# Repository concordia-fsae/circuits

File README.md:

# Circuit Repo
Will contain all of the circuits for the car

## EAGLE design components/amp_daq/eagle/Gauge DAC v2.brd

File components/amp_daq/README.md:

# Strain Gauge Amp Daq Module

Module designed to take in data from strain gauges and ouput over CAN to the Motec.

The last iteration was designed in Eagle (and works), but we will be redesigning in Altium and adding some functionality

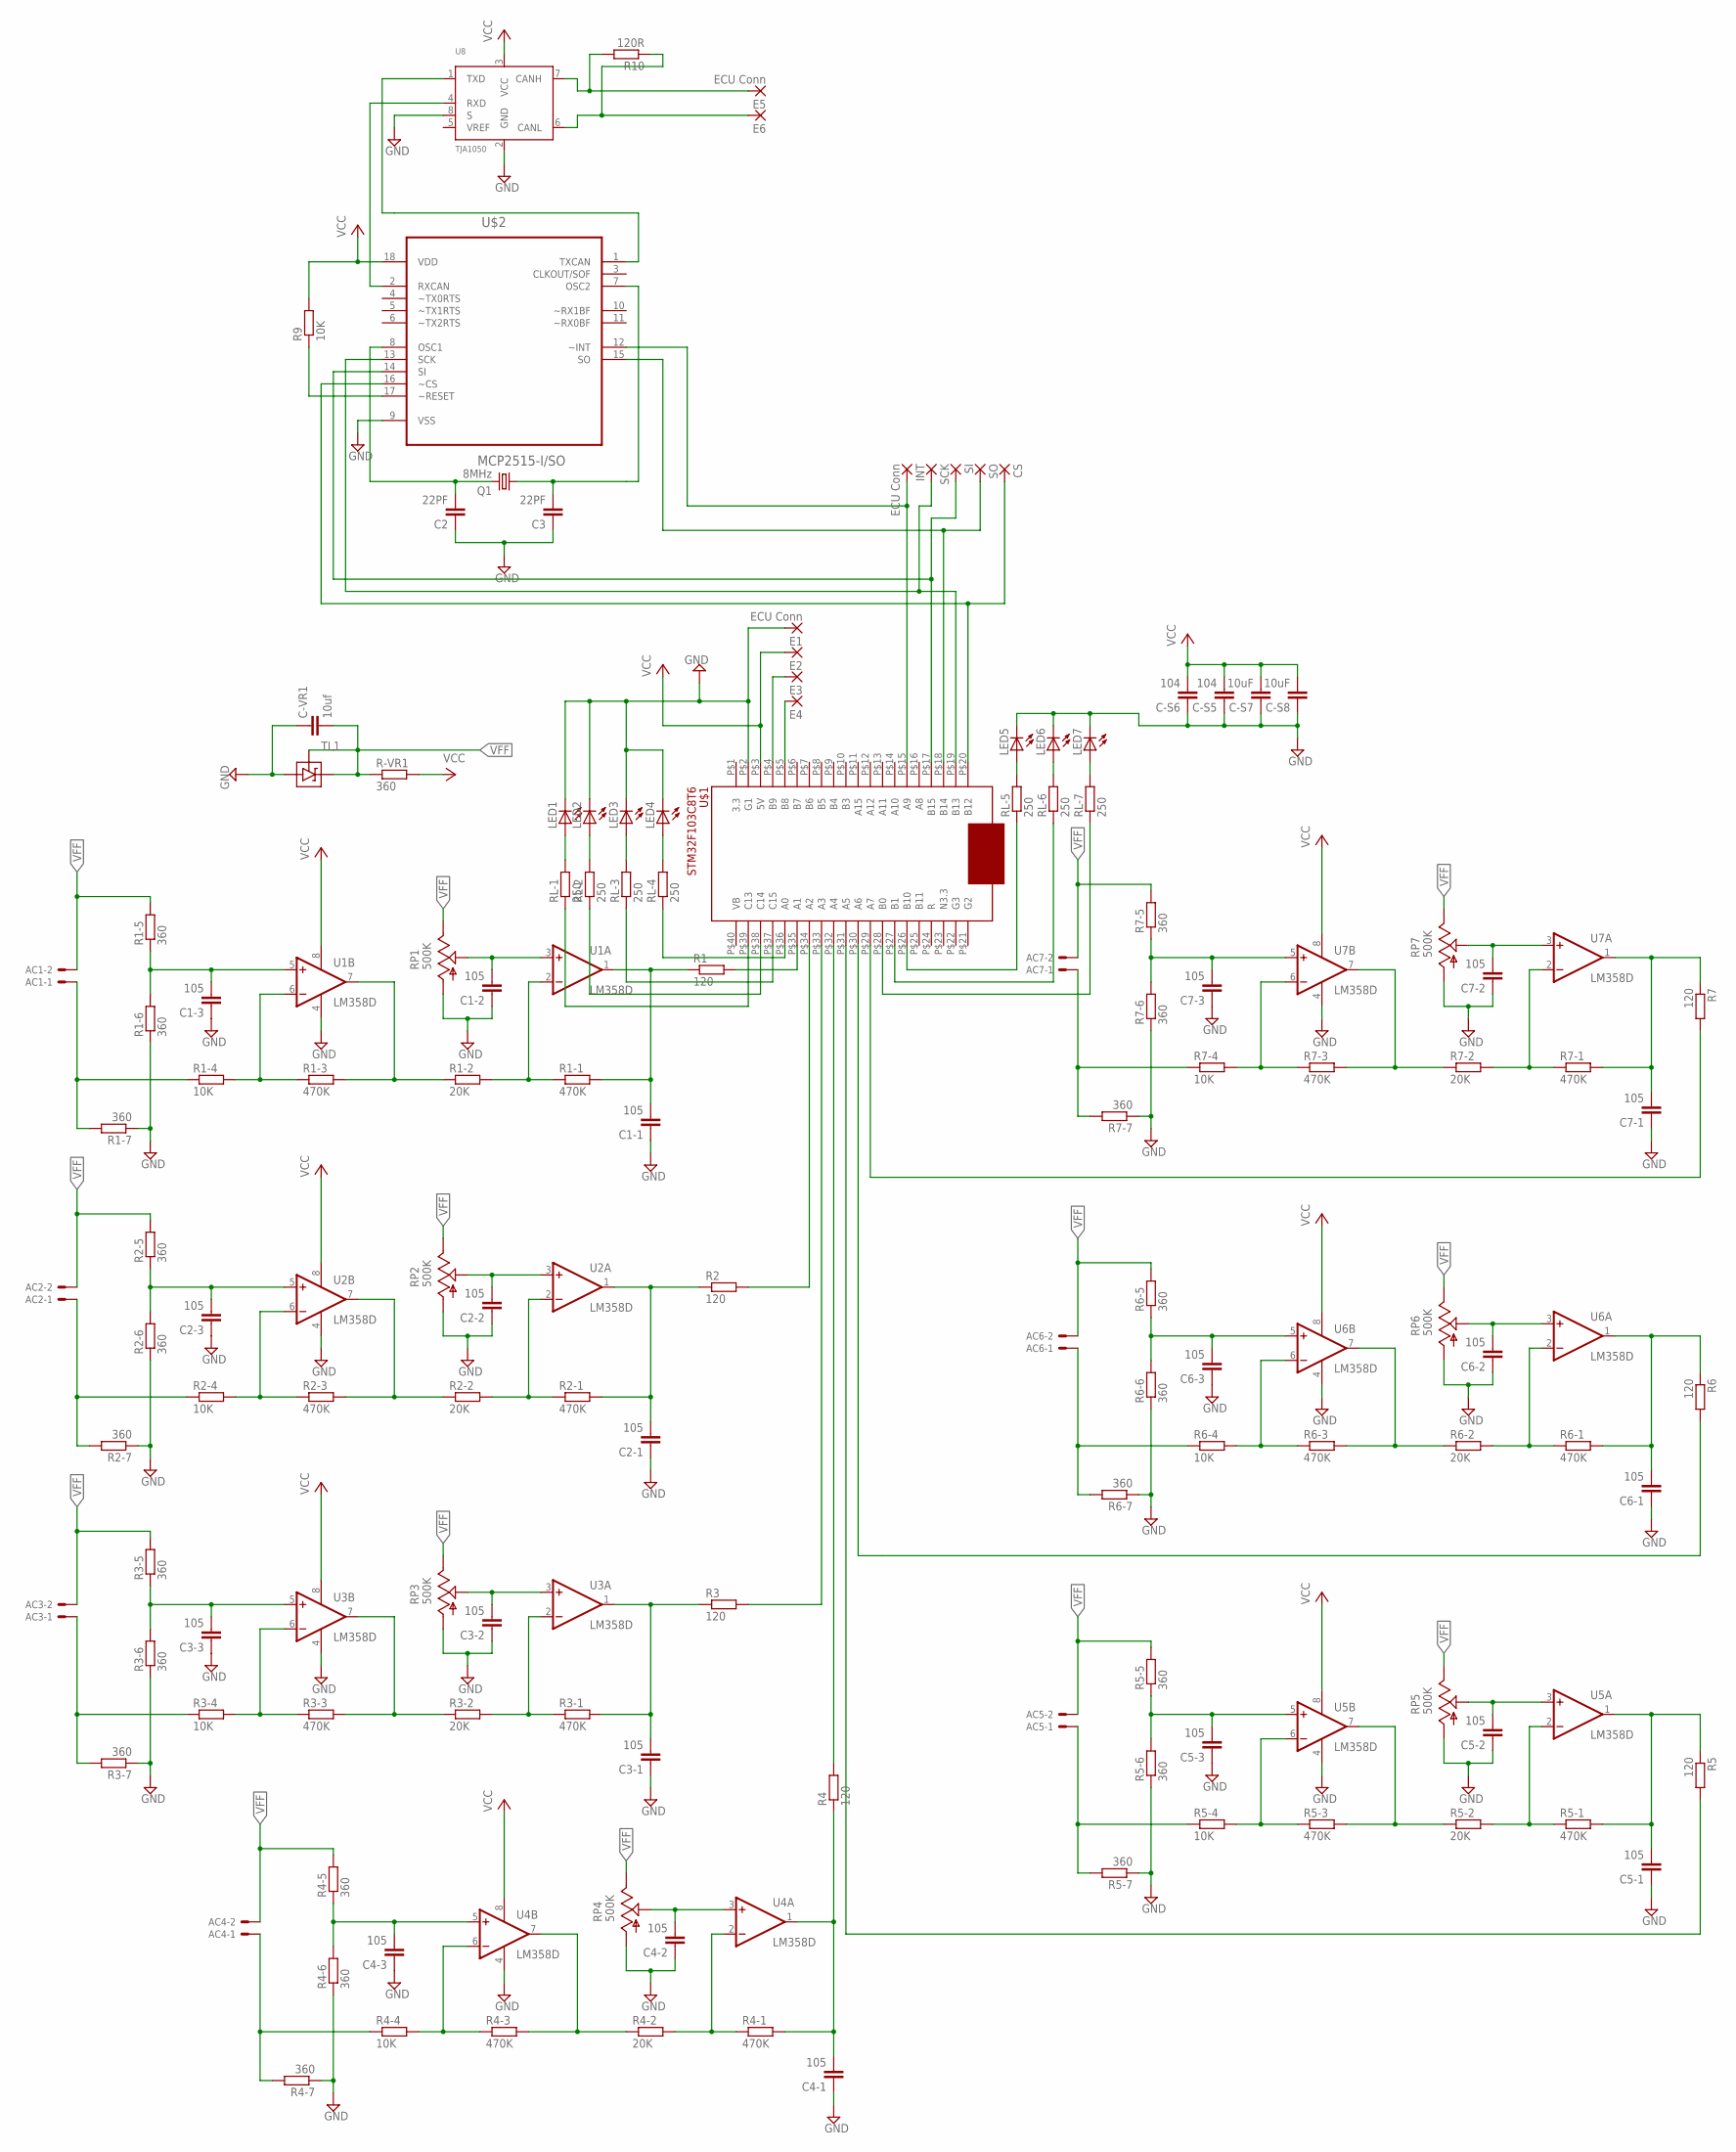
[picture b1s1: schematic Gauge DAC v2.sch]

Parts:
AC1, AC2, AC3, AC4, AC5, AC6, AC7: JST-XH-02-PIN-ROUND-PAD; JST-XH-02-PACKAGE-ROUND-PAD
C1-1, C1-2, C1-3, C2-1, C2-2, C2-3, C3-1, C3-2, C3-3, C4-1, C4-2, C4-3, C5-1, C5-2, C5-3, C6-1, C6-2, C6-3, C7-1, C7-2, C7-3: 105; C0805
C2, C3: 22PF; C0805
C-S5, C-S6: 104; C0805
C-S7, C-S8: 10uF; C0805
C-VR1: 10uf; C0805
CS: WIREPADSMD1,27-254; SMD1,27-2,54
E1, E5: ECU Conn; SMD1,27-2,54
E2, E3, E4: WIREPADSMD1,27-254; SMD1,27-2,54
E6: SMD1,27-2,54
INT: ECU Conn; SMD1,27-2,54
LED1, LED2, LED3, LED4, LED5, LED6, LED7: LEDCHIP-LED0805; CHIP-LED0805
Q1: 8MHz; HC49/S
R1, R2, R3, R4, R5, R6, R7: 120; M0805
R1-1, R1-3, R2-1, R2-3, R3-1, R3-3, R4-1, R4-3, R5-1, R5-3, R6-1, R6-3, R7-1, R7-3: 470K; M0805
R1-2, R2-2, R3-2, R4-2, R5-2, R6-2, R7-2: 20K; M0805
R1-4, R2-4, R3-4, R4-4, R5-4, R6-4, R7-4, R9: 10K; M0805
R1-5, R1-6, R1-7, R2-5, R2-6, R2-7, R3-5, R3-6, R3-7, R4-5, R4-6, R4-7, R5-5, R5-6, R5-7, R6-5, R6-6, R6-7, R7-5, R7-6, R7-7: 360; M0805
R10: 120R; M0805
R-VR1: 360; M0805
RL-1, RL-2, RL-3, RL-4, RL-5, RL-6, RL-7: 250; M0805
RP1, RP2, RP3, RP4, RP5, RP6, RP7: 500K; B64Y
SCK: WIREPADSMD1,27-254; SMD1,27-2,54
SI: WIREPADSMD1,27-254; SMD1,27-2,54
SO: WIREPADSMD1,27-254; SMD1,27-2,54
TL1: TL431SOT23; SOT23
U1, U2, U3, U4, U5, U6, U7: LM358D; SO08
U8: TJA1050; SOT96-1
U$1: STM32F103C8T6DIP40; STM32
U$2: MCP2515-I/SO; SOIC127P1034X264-18N

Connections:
GND: C1-1.1, C1-2.1, C1-3.1, C2.1, C2-1.1, C2-2.1, C2-3.1, C3.1, C3-1.1, C3-2.1, C3-3.1, C4-1.1, C4-2.1, C4-3.1, C5-1.1, C5-2.1, C5-3.1, C6-1.1, C6-2.1, C6-3.1, C7-1.1, C7-2.1, C7-3.1, C-S5.1, C-S6.1, C-S7.1, C-S8.1, C-VR1.1, E1.1, LED1.C, LED2.C, LED3.C, LED4.C, LED5.C, LED6.C, LED7.C, R1-6.1, R1-7.1, R2-6.1, R2-7.1, R3-6.1, R3-7.1, R4-6.1, R4-7.1, R5-6.1, R5-7.1, R6-6.1, R6-7.1, R7-6.1, R7-7.1, RP1.A, RP2.A, RP3.A, RP4.A, RP5.A, RP6.A, RP7.A, TL1.3 (ANODE), U1.4 (V-), U2.4 (V-), U3.4 (V-), U4.4 (V-), U5.4 (V-), U6.4 (V-), U7.4 (V-), U8.2 (GND), U8.8 (S), U$1.P$2 (G1), U$2.9 (VSS)
unnamed: SCK.1, U$1.P$19 (B13), U$2.13 (SCK)
unnamed: CS.1, U$1.P$20 (B12), U$2.16 (~CS)
unnamed: E3.1, U$1.P$4 (B9)
unnamed: E4.1, U$1.P$5 (B8)
unnamed: U8.1 (TXD), U$2.1 (TXCAN)
unnamed: SO.1, U$1.P$18 (B14), U$2.15 (SO)
unnamed: SI.1, U$1.P$17 (B15), U$2.14 (SI)
unnamed: RL-4.1, U$1.P$36 (A0)
unnamed: RL-3.1, U$1.P$37 (C15)
unnamed: C7-1.2, R7.1, R7-1.2, U7.1 (OUT)
unnamed: C1-2.2, RP1.S, U1.3 (+IN)
unnamed: R1-2.1, R1-3.2, U1.7 (OUT)
unnamed: R1-1.1, R1-2.2, U1.2 (-IN)
unnamed: RL-2.1, U$1.P$38 (C14)
unnamed: C1-3.2, R1-5.1, R1-6.2, U1.5 (+IN)
unnamed: R1-3.1, R1-4.2, U1.6 (-IN)
unnamed: AC1.1, R1-4.1, R1-7.2
unnamed: C2-2.2, RP2.S, U2.3 (+IN)
unnamed: R2-2.1, R2-3.2, U2.7 (OUT)
unnamed: R2-1.1, R2-2.2, U2.2 (-IN)
unnamed: C2-1.2, R2.1, R2-1.2, U2.1 (OUT)
unnamed: C2-3.2, R2-5.1, R2-6.2, U2.5 (+IN)
unnamed: R2-3.1, R2-4.2, U2.6 (-IN)
unnamed: AC2.1, R2-4.1, R2-7.2
unnamed: RL-1.1, U$1.P$39 (C13)
unnamed: LED1.A, RL-1.2
unnamed: RL-7.1, U$1.P$28 (B0)
unnamed: RL-6.1, U$1.P$27 (B1)
unnamed: RL-5.1, U$1.P$26 (B10)
unnamed: LED2.A, RL-2.2
unnamed: LED3.A, RL-3.2
unnamed: C3-2.2, RP3.S, U3.3 (+IN)
unnamed: R3-2.1, R3-3.2, U3.7 (OUT)
unnamed: R3-1.1, R3-2.2, U3.2 (-IN)
unnamed: C3-1.2, R3.1, R3-1.2, U3.1 (OUT)
unnamed: C3-3.2, R3-5.1, R3-6.2, U3.5 (+IN)
unnamed: R3-3.1, R3-4.2, U3.6 (-IN)
unnamed: AC3.1, R3-4.1, R3-7.2
unnamed: LED4.A, RL-4.2
unnamed: LED5.A, RL-5.2
unnamed: LED6.A, RL-6.2
unnamed: LED7.A, RL-7.2
unnamed: R9.1, U$2.17 (~RESET)
unnamed: C4-2.2, RP4.S, U4.3 (+IN)
unnamed: R4-2.1, R4-3.2, U4.7 (OUT)
unnamed: R4-1.1, R4-2.2, U4.2 (-IN)
unnamed: C4-1.2, R4.1, R4-1.2, U4.1 (OUT)
unnamed: C4-3.2, R4-5.1, R4-6.2, U4.5 (+IN)
unnamed: R4-3.1, R4-4.2, U4.6 (-IN)
unnamed: AC4.1, R4-4.1, R4-7.2
unnamed: E6.1, R10.1, U8.6 (CANL)
unnamed: U8.4 (RXD), U$2.2 (RXCAN)
unnamed: INT.1, U$1.P$15 (A9), U$2.12 (~INT)
unnamed: C5-2.2, RP5.S, U5.3 (+IN)
unnamed: R5-2.1, R5-3.2, U5.7 (OUT)
unnamed: R5-1.1, R5-2.2, U5.2 (-IN)
unnamed: C2.2, Q1.2, U$2.8 (OSC1)
unnamed: C5-3.2, R5-5.1, R5-6.2, U5.5 (+IN)
unnamed: R5-3.1, R5-4.2, U5.6 (-IN)
unnamed: AC5.1, R5-4.1, R5-7.2
unnamed: C3.2, Q1.1, U$2.7 (OSC2)
unnamed: E5.1, R10.2, U8.7 (CANH)
unnamed: C6-2.2, RP6.S, U6.3 (+IN)
unnamed: R6-2.1, R6-3.2, U6.7 (OUT)
unnamed: R6-1.1, R6-2.2, U6.2 (-IN)
unnamed: C6-3.2, R6-5.1, R6-6.2, U6.5 (+IN)
unnamed: R6-3.1, R6-4.2, U6.6 (-IN)
unnamed: AC6.1, R6-4.1, R6-7.2
unnamed: C7-2.2, RP7.S, U7.3 (+IN)
unnamed: R7-2.1, R7-3.2, U7.7 (OUT)
unnamed: R7-1.1, R7-2.2, U7.2 (-IN)
unnamed: C7-3.2, R7-5.1, R7-6.2, U7.5 (+IN)
unnamed: R7-3.1, R7-4.2, U7.6 (-IN)
unnamed: AC7.1, R7-4.1, R7-7.2
R1: R1.2, U$1.P$35 (A1)
R2: R2.2, U$1.P$34 (A2)
R3: R3.2, U$1.P$33 (A3)
R4: R4.2, U$1.P$32 (A4)
R5: R5.2, U$1.P$31 (A5)
R6: R6.2, U$1.P$30 (A6)
R7: R7.2, U$1.P$29 (A7)
U1-1: C1-1.2, R1.1, R1-1.2, U1.1 (OUT)
U5-1: C5-1.2, R5.1, R5-1.2, U5.1 (OUT)
U6-1: C6-1.2, R6.1, R6-1.2, U6.1 (OUT)
VCC: C-S5.2, C-S6.2, C-S7.2, C-S8.2, E2.1, R9.2, R-VR1.2, U1.8 (V+), U2.8 (V+), U3.8 (V+), U4.8 (V+), U5.8 (V+), U6.8 (V+), U7.8 (V+), U8.3 (VCC), U$1.P$3 (5V), U$2.18 (VDD)
VFF: AC1.2, AC2.2, AC3.2, AC4.2, AC5.2, AC6.2, AC7.2, C-VR1.2, R1-5.2, R2-5.2, R3-5.2, R4-5.2, R5-5.2, R6-5.2, R7-5.2, R-VR1.1, RP1.E, RP2.E, RP3.E, RP4.E, RP5.E, RP6.E, RP7.E, TL1.1 (CATHODE), TL1.2 (REF)

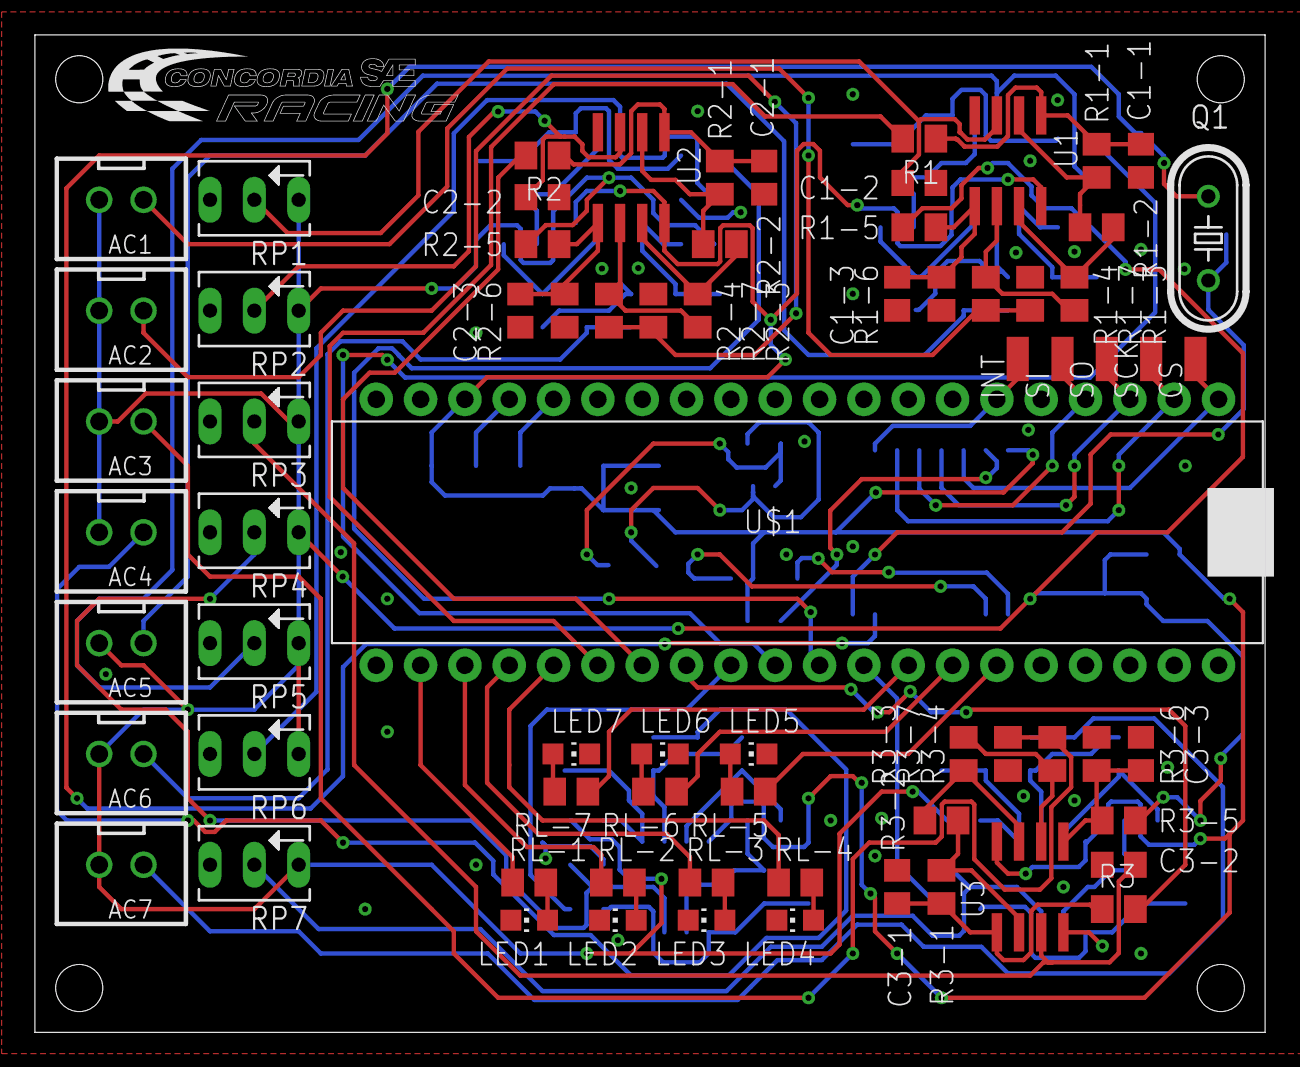
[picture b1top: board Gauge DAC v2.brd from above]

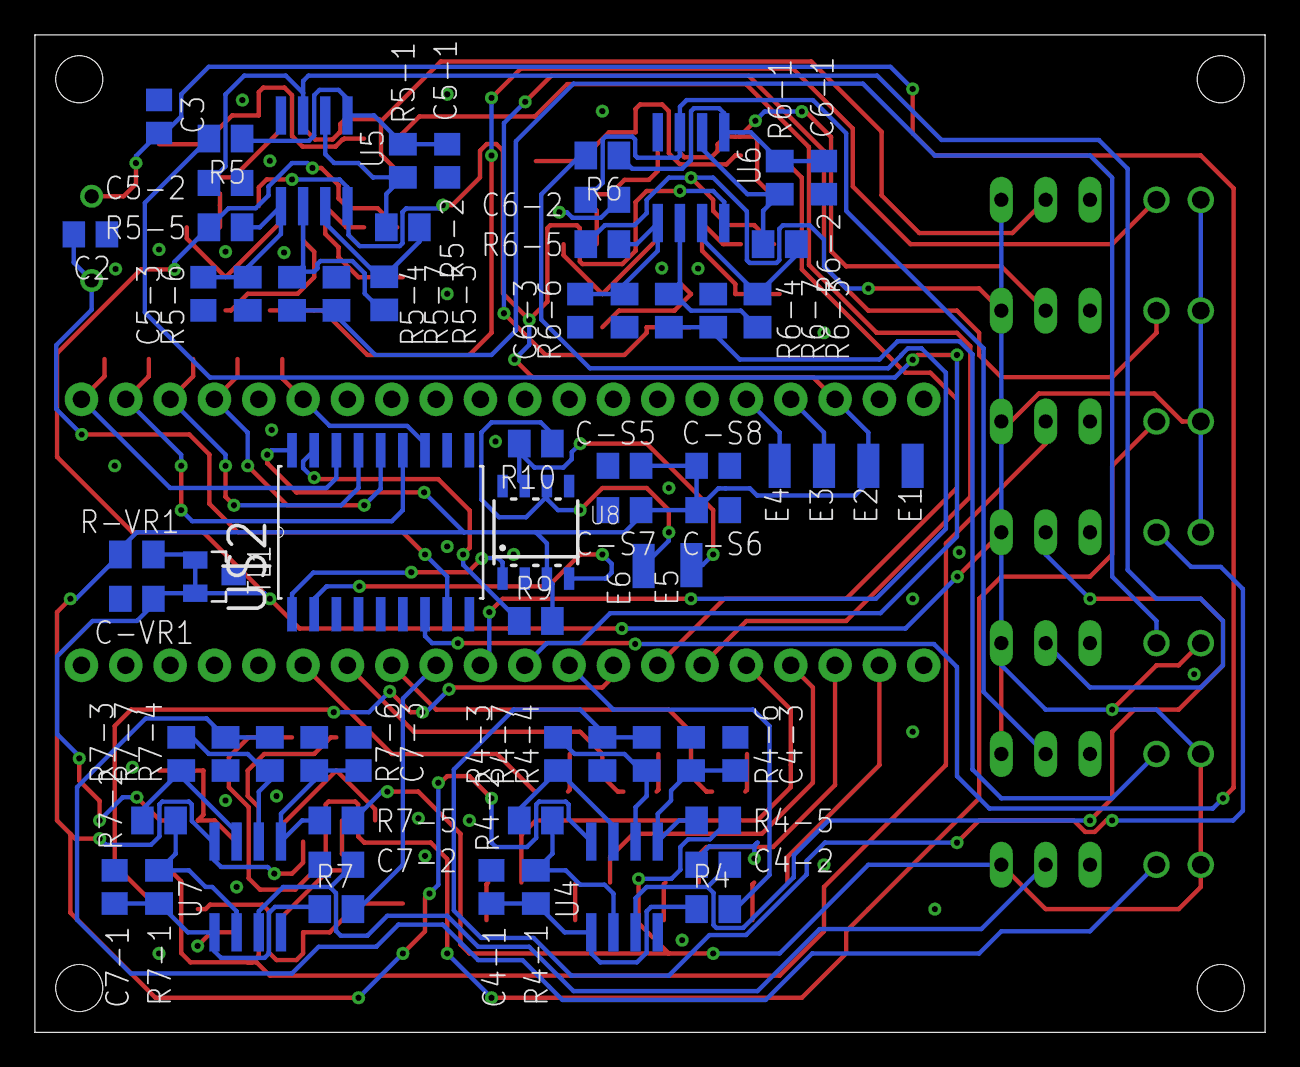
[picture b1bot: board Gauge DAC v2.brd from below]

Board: 2 copper layers, 70.5 x 57.1 mm, 138 parts (67 on the bottom side), 87 nets.

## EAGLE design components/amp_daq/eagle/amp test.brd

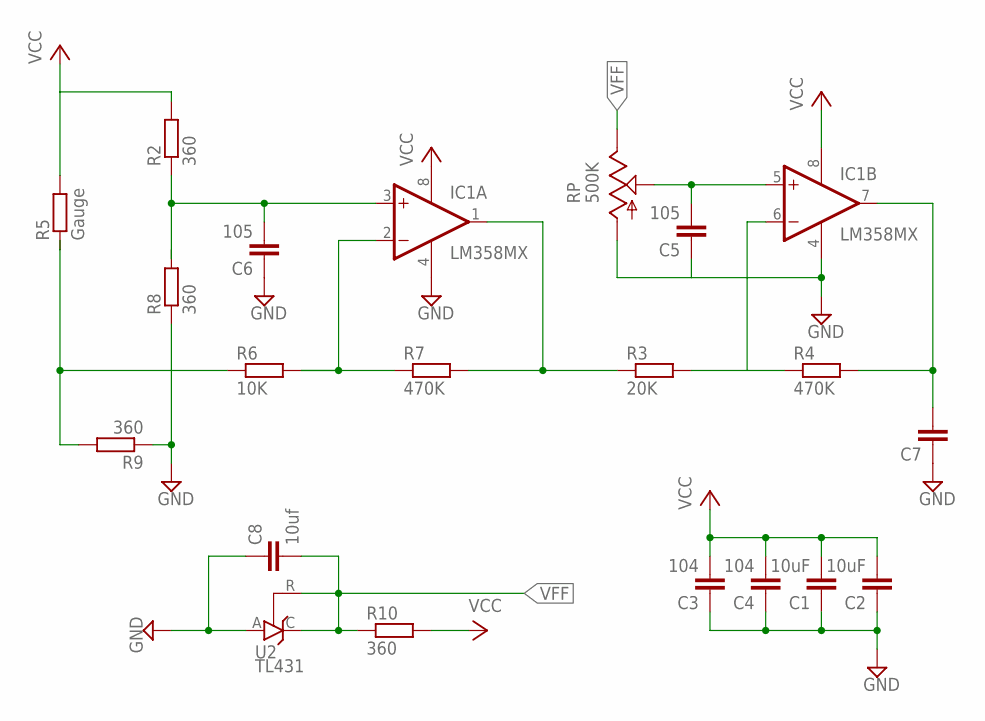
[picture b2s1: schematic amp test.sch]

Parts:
C1, C2: 10uF; C0805
C3, C4: 104; C0805
C5, C6: 105; C0805
C7: C-EUC0805; C0805
C8: 10uf; C0805
IC1: LM358MX; SO08
IC2: LM358D; SO08
R2, R8, R9, R10: 360; M0805
R3: 20K; M0805
R4, R7: 470K; M0805
R5: Gauge; M0805
R6: 10K; M0805
RP: 500K; B64Y
U2: TL431; TO92-CLP

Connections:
GND: C1.1, C2.1, C3.1, C4.1, C5.1, C6.1, C7.1, C8.1, IC1.4 (V-), R8.1, R9.1, RP.A, U2.A
unnamed: IC1.1 (OUT), R3.1, R7.2
unnamed: C5.2, IC1.5 (+IN), RP.S
unnamed: IC1.6 (-IN), R3.2, R4.1
unnamed: C7.2, IC1.7 (OUT), R4.2
unnamed: C6.2, IC1.3 (+IN), R2.1, R8.2
unnamed: IC1.2 (-IN), R6.2, R7.1
unnamed: R2.2, R5.2
unnamed: R5.1, R6.1, R9.2
V+: IC2.8 (V+)
V-: IC2.4 (V-)
VCC: C1.2, C2.2, C3.2, C4.2, IC1.8 (V+), R10.2
VFF: C8.2, R10.1, RP.E, U2.C, U2.R

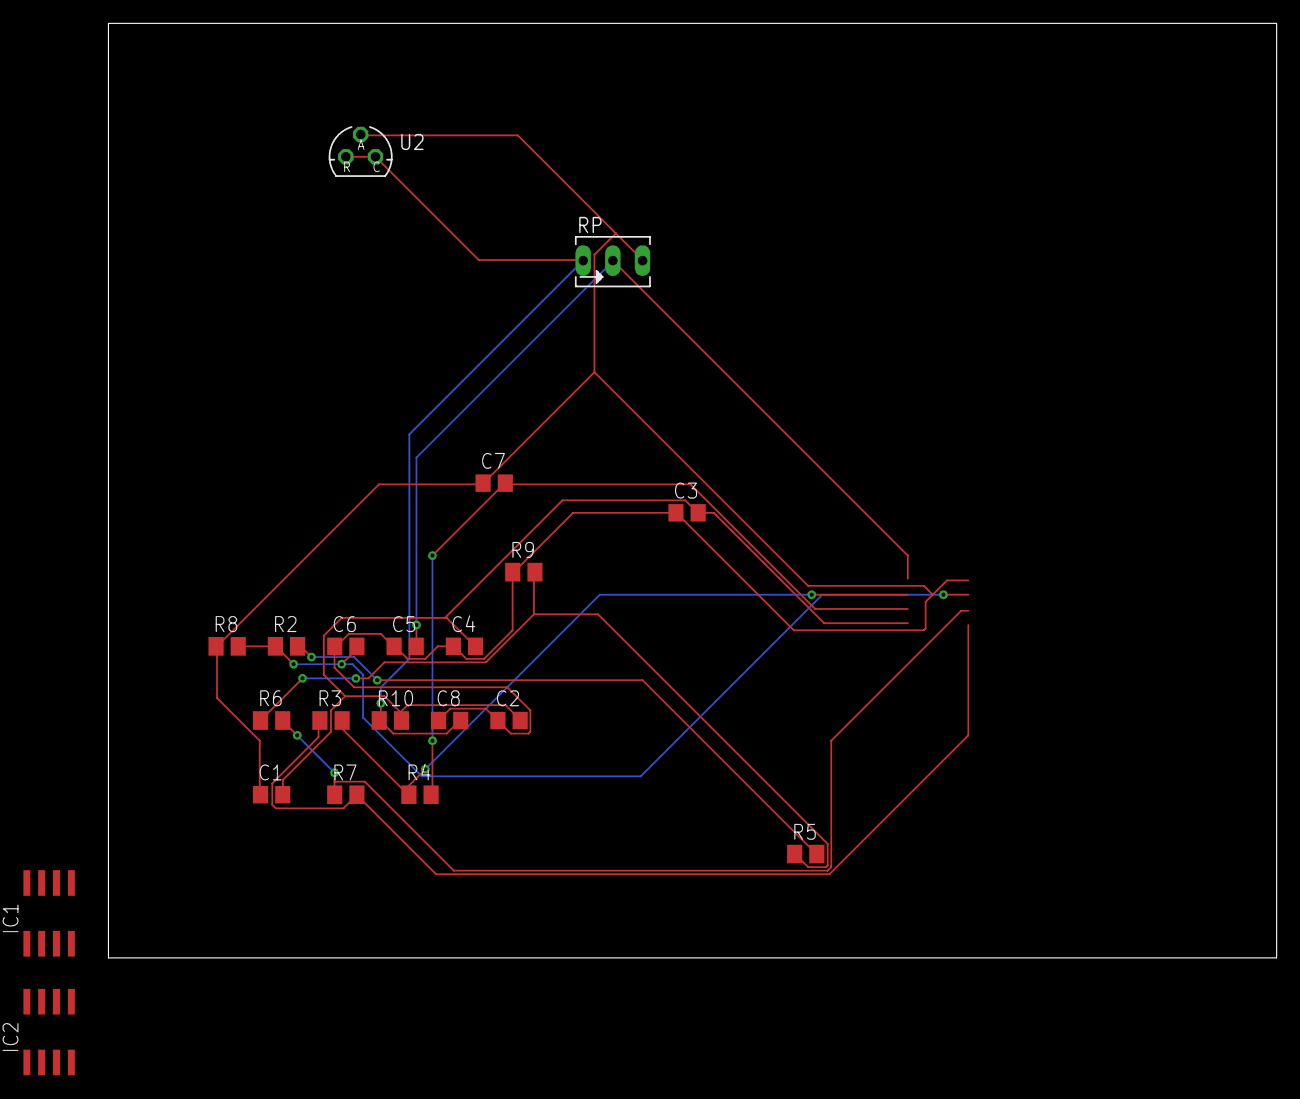
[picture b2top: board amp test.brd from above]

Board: 2 copper layers, 100.0 x 80.0 mm, 21 parts (0 on the bottom side), 11 nets.

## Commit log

2020-12-31 starting up the repo
2020-12-31 added steering wheel and strain gauge amp stuff
2020-12-31 added sensor to can documentation
2021-02-07 AmpDAQstartup
2021-12-30 steering wheel board v1 as manufactured using STM32 again, with builtin CAN peripheral
